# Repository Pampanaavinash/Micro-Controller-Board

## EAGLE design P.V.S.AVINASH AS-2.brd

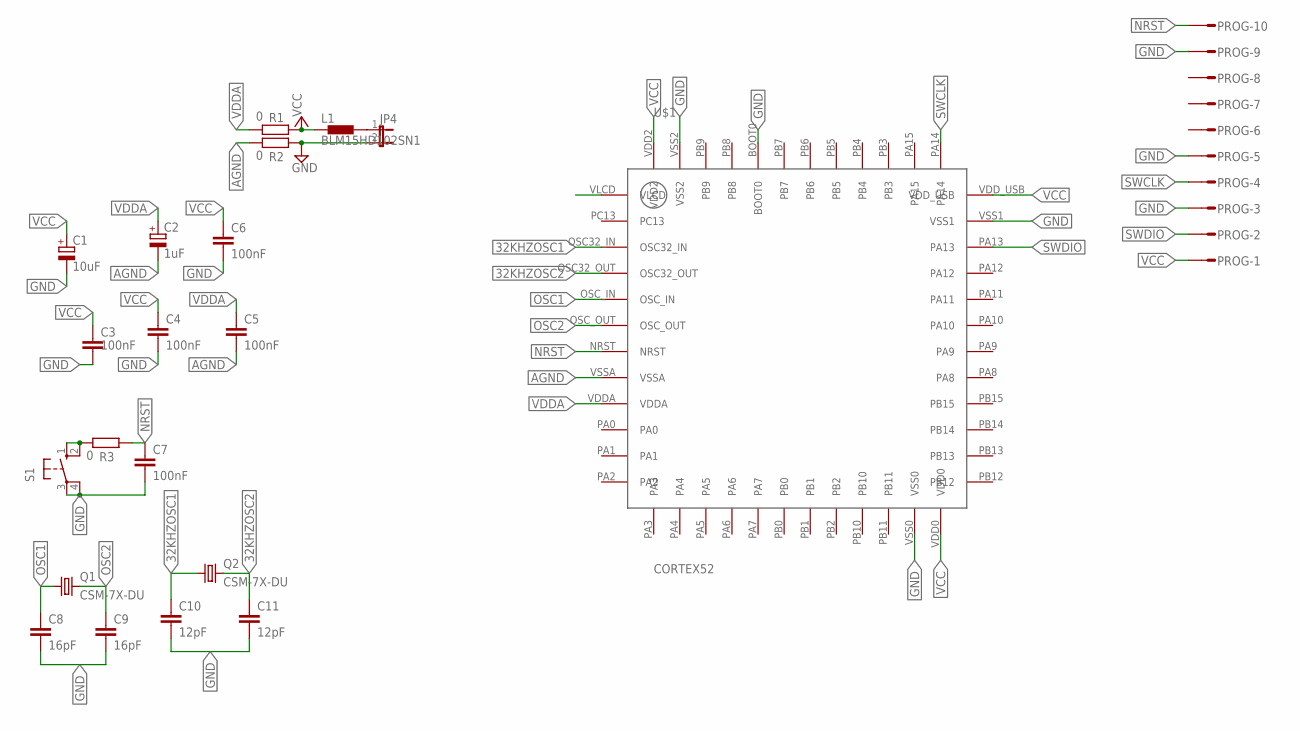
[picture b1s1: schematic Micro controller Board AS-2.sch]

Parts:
C1: 10uF; 139CLL-2R
C2: 1uF; 139CLL-2R
C3, C4, C5, C6, C7: 100nF; C0805
C8, C9: 16pF; C0805
C10, C11: 12pF; C0805
JP4: JP1E; JP1
L1: BLM15HD102SN1; 0402
PROG: S10P
Q1, Q2: CSM-7X-DU
R1, R2, R3: 0; R0805
S1: 10-XX; B3F-10XX
U$1: CORTEX52

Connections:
32KHZOSC1: C10.1, Q2.1, U$1.OSC32_IN
32KHZOSC2: C11.1, Q2.2, U$1.OSC32_OUT
AGND: C2.-, C5.2, R2.1, U$1.VSSA
GND: C1.-, C3.2, C4.2, C6.2, C7.2, C8.2, C9.2, C10.2, C11.2, JP4.2, PROG.3, PROG.5, PROG.9, R2.2, S1.3, S1.4 (P1), U$1.BOOT0, U$1.VSS0, U$1.VSS1, U$1.VSS2
unnamed: JP4.1, L1.2
unnamed: R3.1, S1.1 (S), S1.2 (S1)
NRST: C7.1, PROG.10, R3.2, U$1.NRST
OSC1: C8.1, Q1.1, U$1.OSC_IN
OSC2: C9.1, Q1.2, U$1.OSC_OUT
SWCLK: PROG.4, U$1.PA14
SWDIO: PROG.2, U$1.PA13
VCC: C1.+, C3.1, C4.1, C6.1, L1.1, PROG.1, R1.2, U$1.VDD0, U$1.VDD2, U$1.VDD_USB
VDDA: C2.+, C5.1, R1.1, U$1.VDDA

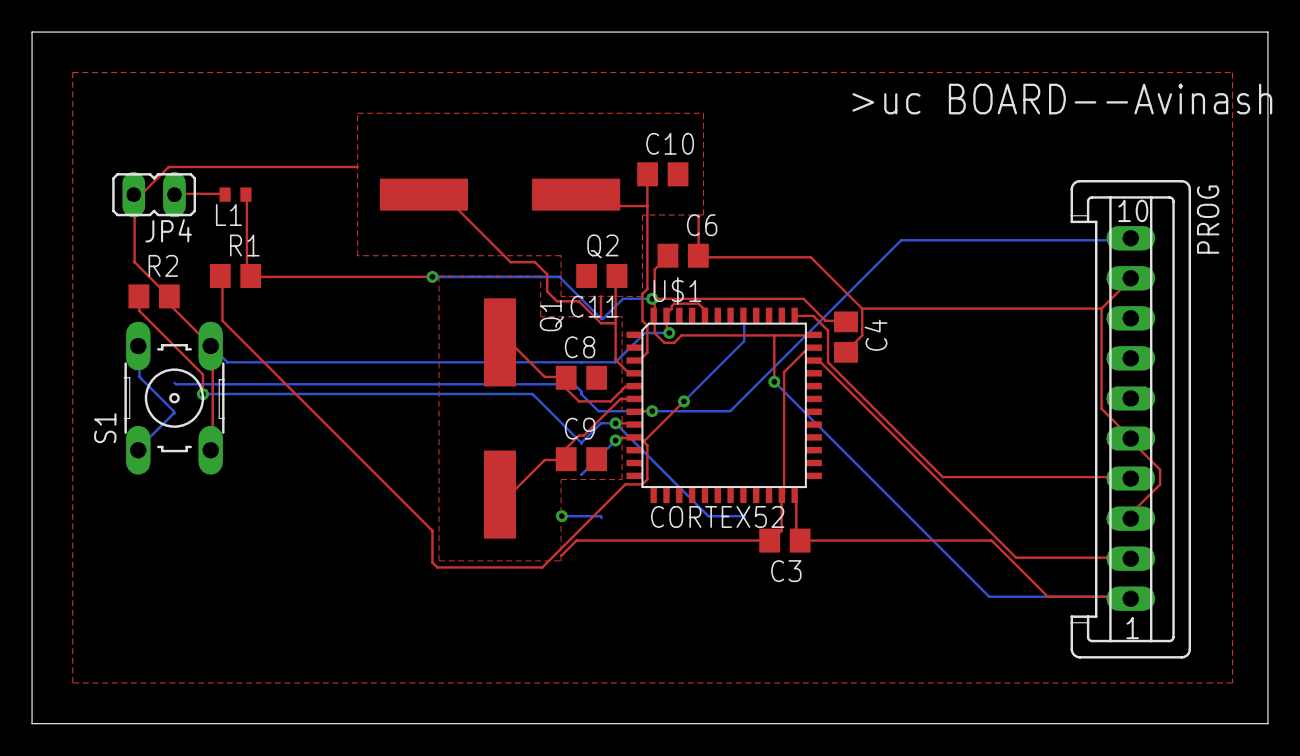
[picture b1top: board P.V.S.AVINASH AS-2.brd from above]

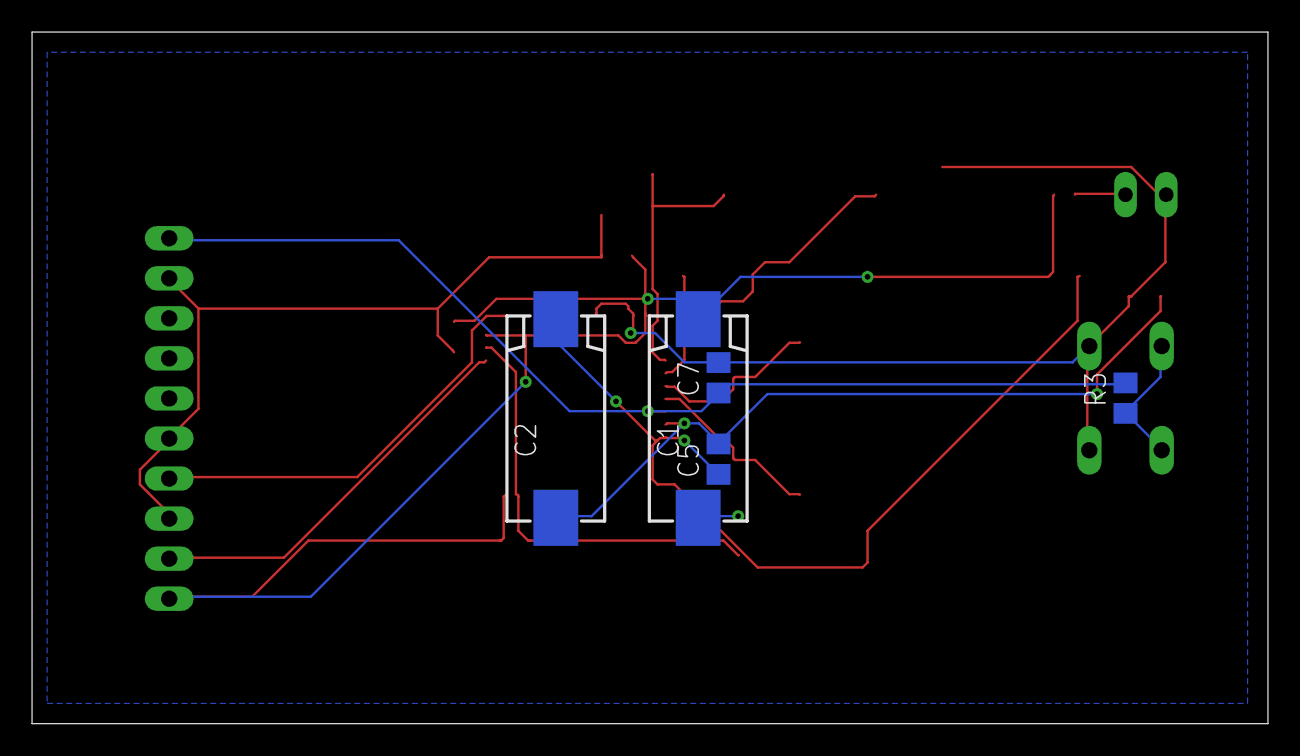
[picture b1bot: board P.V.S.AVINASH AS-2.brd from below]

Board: 2 copper layers, 77.1 x 43.2 mm, 21 parts (5 on the bottom side), 13 nets.

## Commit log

2024-02-29 Micro controller Board Gerber Files
